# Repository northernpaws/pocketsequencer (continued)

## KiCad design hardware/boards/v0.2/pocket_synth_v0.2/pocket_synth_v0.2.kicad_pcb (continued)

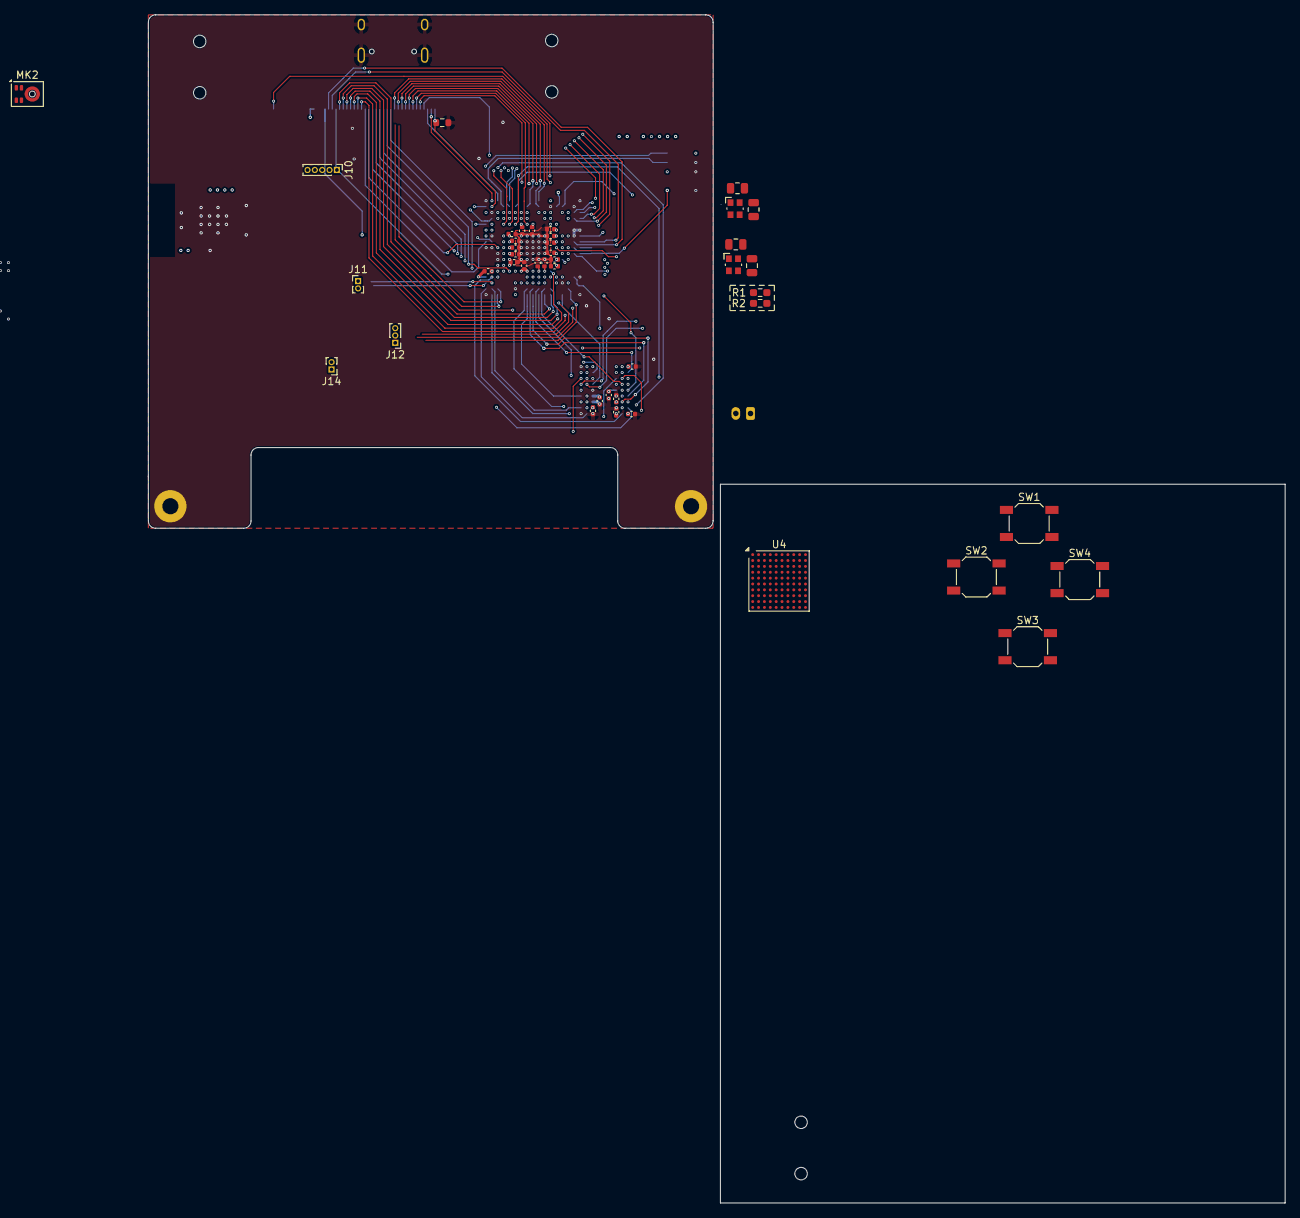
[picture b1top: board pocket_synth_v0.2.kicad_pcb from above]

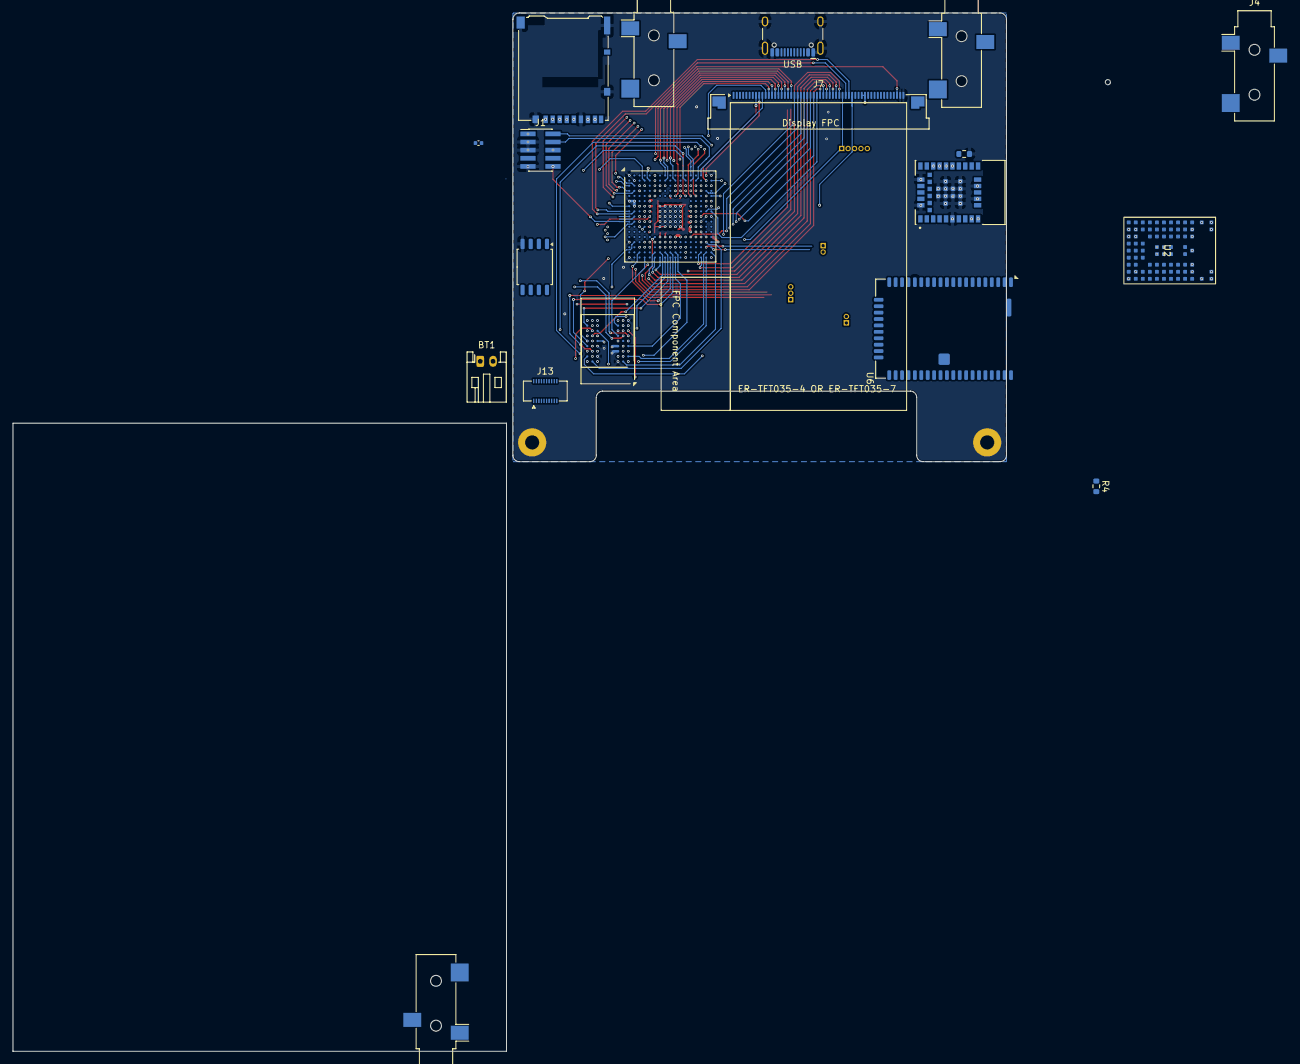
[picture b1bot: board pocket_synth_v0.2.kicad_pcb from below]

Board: 6 copper layers, 155.0 x 162.0 mm, 64 parts (19 on the bottom side), 120 nets.

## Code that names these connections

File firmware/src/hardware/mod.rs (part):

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    /// Primary I2S interface, to NAU88C22YG audio codec.
    codec: CodecResources {
        peri: SAI1 = CodecPeri,
        mclk: PG7, // SAI1_MCLK_A
        adcdat: PE3, // SAI1_SD_B
        fs: PE4, // SAI1_FS_A
        sck: PE5, // SAI1_SCK_A,
        dacdat: PE6, //  SAI1_SD_A

        mic_l: PC8, // HIGH = mic-level input
        mic_r: PC7, // HIGH = mic-level input
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
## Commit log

2025-09-05 feat: start adding hardware directory
2025-09-05 feat: start adding firmware directory
2025-09-06 feat: import board and library from previous revision, start board modifications
2025-09-07 feat: various component and layout changes
2025-09-07 feat: add menu buttons and speaker connectors
2025-09-08 feat: schematic organization
2025-09-08 feat: try routing vertically with bit swapping
2025-09-08 feat: add bulk of SDRAM routing
2025-09-08 feat: finish routing SDRAM
2025-09-08 feat: SDRAM routing cleanup
2025-09-08 feat: start MIDI and CV schematic
2025-09-09 feat: various schematic organization
2025-09-09 feat: schematic organization, MIDI port routing
2025-09-09 feat: route audio components
2025-09-09 feat: start adding FM receiver
2025-09-09 feat: add codec 3D model
2025-09-10 feat: FM receiver routing
2025-09-11 feat: FM transmitter and routing
2025-09-11 feat: route dedicated audio I2C bus
2025-09-11 fix: I2C routing for keypad
2025-09-11 fix: set different I2C addresses for FM ICs
2025-09-11 fix: DRC drill clearance errors
2025-09-11 feat: power system routing
2025-09-11 feat: SD card SPI bus and routing
2025-09-11 chore: move debug connectors
2025-09-12 feat: start adding Wifi module
2025-09-12 feat: various routing and organization
2025-09-12 feat: schematic organization and ERC cleanup
2025-09-12 feat: add missing power button controller
2025-09-13 feat: add test points and top and bottom ground pours
2025-09-13 feat: add more test points
2025-09-13 feat: add touch screen connector, input I2C bus
2025-09-13 feat: remove bitmagic connector
2025-09-13 feat: add IO expander for velocity pads
2025-09-13 chpre: remove extraneous ground vias
2025-09-13 feat: various ERC and DRC cleanup
2025-09-13 fix: incorrect symbol defined for MCU
2025-09-13 fix: more ERC cleanup
2025-09-14 feat: remove analog MIDI thru
2025-09-14 feat: more routing and DRC cleanup
2025-09-14 feat: more DRC cleanup
2025-09-14 feat: finally add power button!
2025-09-14 chore: add PCB routing notes
2025-09-14 chore: add more notes
2025-09-14 feat: switch FM transmitter to I2S
2025-09-14 feat: add FM reset pins, add fiducials
2025-09-14 feat: add display reset connection
2025-09-14 feat: change FM receiver to newer model with RDS
2025-09-14 chore: make ERC happy
2025-09-15 feat: route thermalcouple, add top side fiducials
2025-09-15 feat: add USB-PD source mode boost converter, mosets, and PD controller
2025-09-16 feat: add USB-PD power distribution switches
2025-09-17 feat: route USB-PD power distribution switches and boost converter
2025-09-18 chore: update power notes
2025-09-18 feat: clean up routing, remove metronome light
2025-09-19 feat: routing cleanup and start of BOM selection
2025-09-20 feat: update various components to 0402
2025-09-20 feat: various DFM cleanup steps
2025-09-20 chore: update board v0.1 README.md
2025-09-21 feat: various routing cleanup, add SD flash
2025-09-22 chore: more schematic and routing organization
2025-09-22 feat: set correct footprint for matrix diodes
2025-09-22 feat: more BOM selection
2025-09-23 feat: swap out of stock components
2025-09-24 feat: various cleanup and BOM adjustment, split audio in into two switches
2025-09-24 feat: fix RGB LED circuit
2025-09-24 feat: add haptic transducer DAC
2025-09-25 chore: schematic cleanup
2025-09-26 feat: add LCD backlight control
2025-09-26 feat: reduce via-in-pads
2025-09-26 feat: add power LEDs and adjust layout
2025-09-29 feat: change charger, fuel gauge, and battery connector, re-route power system
2025-09-29 chore: adjust power zone fills
2025-09-30 feat: more layout of new power circuit
2025-09-30 chore: more power layout
2025-10-03 feat: finish routing new power circuit
2025-10-05 feat: various layout and routing adjustments
2025-10-05 chore: various jlcdfm adjustments
2025-10-06 chore: more DFM tweaks
2025-10-07 feat: add pins in silkscreen, various DFM adjustments for JLC
2025-10-07 chore: update .gitignore
2025-10-07 chore: add JLC rotation and position offsets
2025-10-07 chore: remove unused symbol attributes
2025-10-07 fix: rotation offsets and LEDs on wrong side of board
2025-10-07 fix: accidentally excluding switches from board
2025-10-08 chore: remove BOM excluded components from positions file
2025-10-08 chore: extra doc comments
2025-10-08 feat: add LDO for MCU VBAT
2025-10-08 feat: route LDO for MCU VBAT
2025-10-08 chore: remove old VBAT callout
2025-10-08 feat: various SMD DFM fixes
2025-10-09 chore: add missing datasheet for FM receiver
2025-10-09 chore: final DFM modifications?
2025-10-09 feat: production export
2025-10-22 chore: document errata for v0.1 boards
2025-10-22 feat: start implementing hardware interface for v0.1 board firmware
2025-10-23 feat: add display and USB_HS driver constructors
2025-10-23 feat: add STM6601 and SPI SD drivers, start adding keypad driver
2025-10-23 feat: start implementing TCA8418 registers
2025-10-23 feat: implement TCA8418 init and general cleanup
2025-10-23 chore: add keypad errata to v0.1 README.md
2025-10-23 chore: cleanup and documentation of initialization order
2025-10-24 feat: start adding bq27531-G1 driver
2025-10-24 feat: fix b1s7531-g1 command codes
2025-10-24 feat: start adding basic fusb302b driver
2025-10-24 feat: change fusb302b registers to use proc_bitfield for better safety
2025-10-26 feat: fix PLL config, integrate keypad LEDs
2025-10-26 chore: working on internal flash
2025-10-26 feat: start fixing internal SD storage library in fork
2025-10-26 feat: make unified interface for SD card
2025-10-27 feat: start adding MBR support to SD card
2025-10-27 feat: sd card filesystem support wrapper
2025-10-27 feat: basic USB MIDI test
2025-10-27 feat: add USB MIDI decoding
2025-10-27 feat: fix keypad LED interface to use task
2025-10-27 feat: fix SDRAM parameters and enable
2025-10-27 chore: move hardware drivers into `drivers` module
2025-10-27 feat: add NAU88C22YG registers
2025-10-28 feat: start adding nrf5340 bluetooth firmware
2025-10-28 feat: add nRF Connect BSP for board
2025-10-30 feat: implement keypad matrix processing loop
2025-10-30 feat: start implementing engine interface
2025-10-31 feat: dynamically calculate LED PWM period
2025-11-01 feat: working display implementation
2025-11-03 feat: basic FMC-based display driver implemented
2025-11-04 half-finished display DMA transfers
2025-11-04 finish display DMA transfer code via forked interface
2025-11-04 before remapping sram to device memory space
2025-11-04 working parallel display interface with DMA over FMC
2025-11-05 various display clock tweaks
2025-11-05 optimize fill operations for 31x speed increase
2025-11-05 move USB buffer to recommended SRAM3 section
2025-11-05 add heap allocator :(
2025-11-05 enable SDRAM with display SRAM
2025-11-05 add boot status screen
2025-11-06 start adding diagnostics menu
2025-11-08 start of various code cleanups
2025-11-10 keypad logic overhaul
2025-11-10 fix incorrect keypad light colors
2025-11-10 fix boot sequence not catching input events
2025-11-10 implement input diagnostics menu
2025-11-10 start adding battery diagnostics menu
2025-11-30 add power management component, try to configure charger and fuel gauge
2025-11-30 add missing README.md details
2025-11-30 add board schematic and errata links to README.md
2025-11-30 add images to README.md
2025-11-30 fix format of README.md image tags
2025-11-30 align README images side by side
2025-12-15 add note to README.md about rythm
2025-12-26 add registers to battery diagnostics
2025-12-27 update audio component to use new `nau88c22-rs` crate
2025-12-27 remove previous display driver
2025-12-27 initialize audio component
2025-12-27 start configuring audio components
2025-12-27 first working audio config!
2025-12-27 comment out audio test code
2025-12-28 SAI still overflowing
2025-12-28 split audio codec out into seperate bin to test
2025-12-28 before audio refractor
2025-12-28 after audio refractor
2025-12-29 update to latest `embassy-stm32`, `embedded-io`, and `embedded-io-async` dependencies
2025-12-29 fix SAI config for i2s protocol
2025-12-29 fixed audio via `iobufen` flag being cleared by `nau88c22` library erroneously
2025-12-29 working audio playback example
2025-12-29 fix sample format conversion
2025-12-29 fold working audio code into hardware driver, cleanup imports
2025-12-29 correct audio component usage in main program
2025-12-29 clean up keypad constructors
2025-12-29 working internal storage driver
2025-12-31 fixed SAI buffer overrun with `opt-level` > 0
2026-01-01 use PLL fractional multiplier for SAI1
2026-01-01 update codec config to use new utility methods
2026-01-01 fix zero gain on DAC output
2026-01-01 start adding crate for graphics components
2026-01-01 move hardware initialization into `hardware` module, start adding primary program tasks
2026-01-01 automatically format internal storage if filesystem is invalid
2026-01-01 various cleanup and migration to application loops
2026-01-05 laid out ideas for hardware v0.2
2026-01-05 various firmware reorganization
2026-01-06 integrate USB midi into new project layout
2026-01-06 initialize heap and start using for some channel messages types
2026-01-06 implement filesystem command response channel
2026-01-07 add read file filesystem command
2026-01-07 add directory listing filesystem task
2026-01-07 implement streaming read/write in filesystem
2026-01-07 add filesystem interface wrapper
2026-01-07 add convenience wrapper for filesystem drive methods
2026-01-07 add more alias types to simplify higher-level calls
2026-01-07 foundations of midi routing table
2026-01-08 wrap midi source and destination channels in struct
2026-01-08 wrap MIDI destination receiver and source sender into `MIDIEndpoint` struct
2026-01-08 move MIDI channel setup into MIDI subsystem constructor
2026-01-08 move drive channel construction into drive constructor
2026-01-08 add missing await on MIDI sender
2026-01-08 add drive error type and simplify task
2026-01-08 extract codec config management to seperate task
2026-01-08 rename firmware folders
2026-01-14 add USB MIDI sender task
2026-01-14 fix heap using stack address pointer
2026-01-15 start implementing system sound mixing
2026-01-15 semi-working startup playback
2026-01-15 resolved system audio playback routine buzzing
2026-01-16 fix sending unsigned audio data to signed i2s peripheral causing audio quality issues
2026-01-19 start rev2 schematic and layout
2026-01-19 cleanup audio playback code
2026-01-19 update v0.1 errata
2026-01-20 start SDRAM routing
2026-01-20 routed right side of SDRAM
2026-01-21 more SDRAM routing
2026-01-22 finish routing SDRAM
2026-01-22 routed display FPC
2026-01-25 more display connector routing
2026-01-26 routing of various peripherals
2026-01-27 add NINA-W13 Wifi module and BM83 Bluetooth Audio
